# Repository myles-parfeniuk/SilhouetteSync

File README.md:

<ol>
  <li><a href="#about">About</a></li>
  <li><a href="#to-do">To Do</a>
    <ul>
      <li><a href="#hardware">Hardware</a></li>
      <li><a href="#software">Software</a></li>
      <li><a href="#firmware">Firmware</a></li>
    </ul>
  </li>
  <li><a href="#license">License</a></li>
</ol>

## About
Open source motion tracker band intended for athletics analytics.

## To Do

### Hardware
- Decide on full breadth of features ✔️
- Finalize IMU selection ✔️
- Determine user inputs ✔️
- Finalize schematic ✔️
- Finalize layout✔️
- First PCB bring-up
- Test power draw for battery selection
- Design device enclosure

### Software
- Attempt basic plotting ✔️ 
- Decide on choice of language ✔️
- Decide on choice of graphics rendering or plotting library ✔️
- Test animation and basic app layout ✔️
- Write backend for communication with firmware (for prototyping UART/serial can be used)
- Algorithm to derive individual joint angle regardless of absolute body position
- Algorithm to follow through workout and report on effectiveness
- Tracker information screen
 
### Firmware
- Run tests and determine whether WiFi or BLE will be used to communicate with software ✔️
- Write driver for BLE or UDP (maybe TCP?) over WiFi ✔️
- Write driver class for BNO085 SPI IMU ✔️
- Implement addressable LEDs ✔️
- Write battery gauge driver (decided to go with ADC battery measurement)
- Write suit calibration routine 
- Improve wireless stability
- Implement device power up and power sensing algorithm

## License
Distributed under the GNU 3.0 License. See `LICENSE.md` for more information.
<p align="right">(<a href="#readme-top">back to top</a>)</p>

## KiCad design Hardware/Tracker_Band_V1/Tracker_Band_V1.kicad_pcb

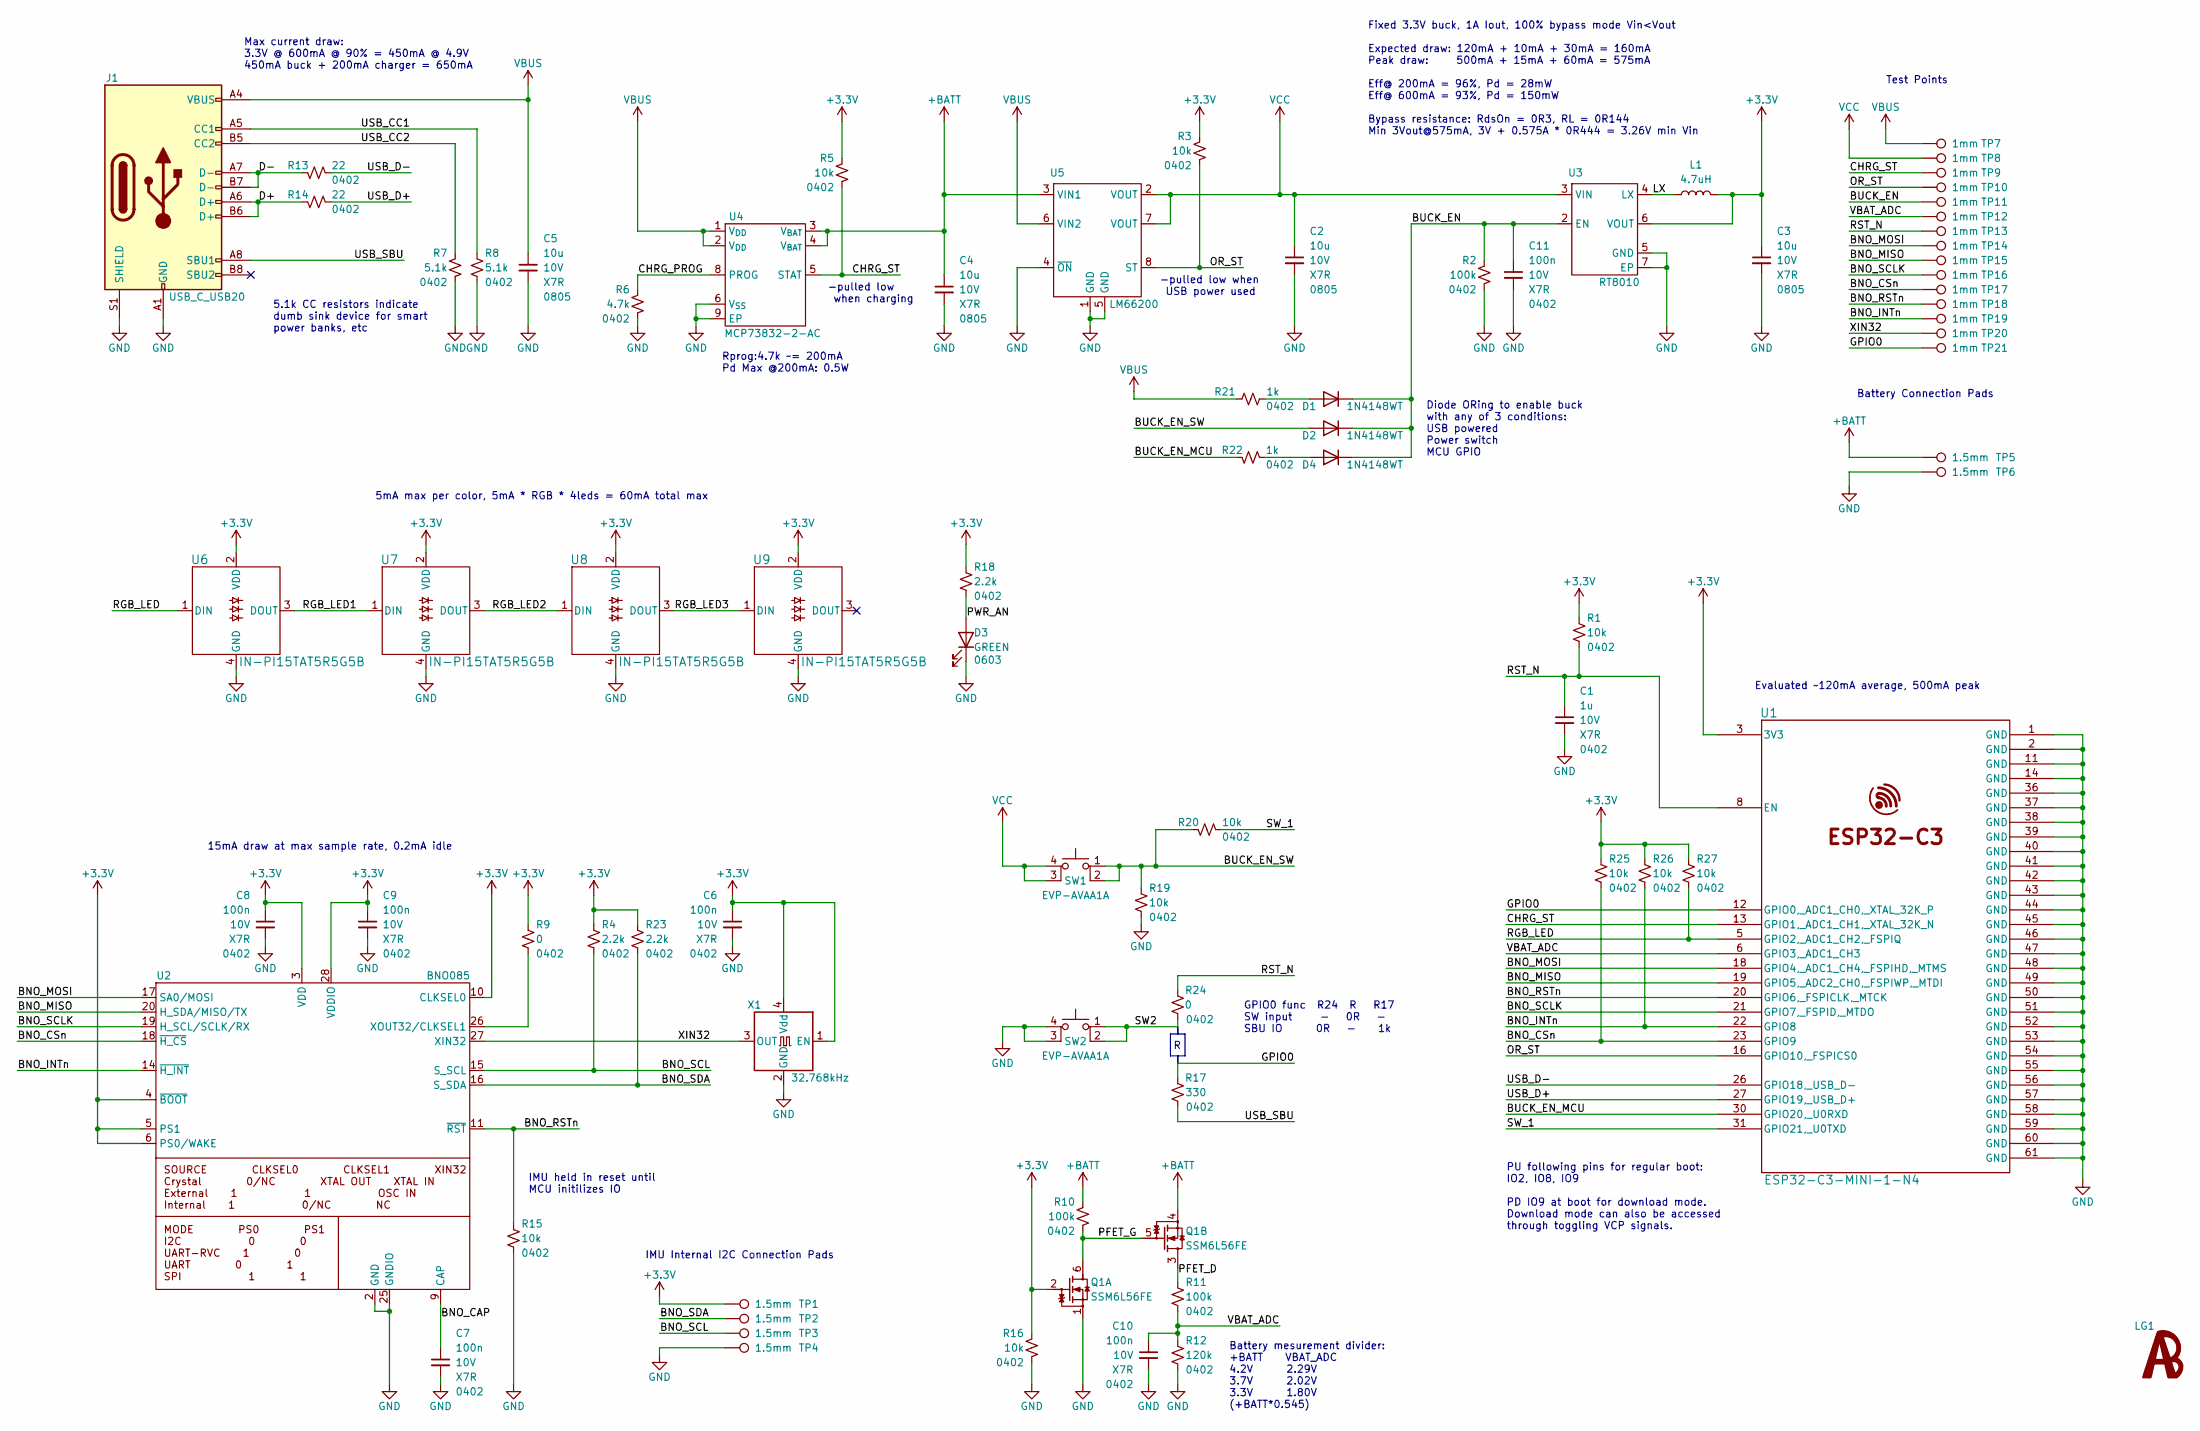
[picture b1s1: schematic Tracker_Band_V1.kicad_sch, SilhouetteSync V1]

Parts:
C1: 1u; C_0402_1005Metric; Voltage 10V
C2, C3, C4, C5: 10u; C_0805_2012Metric; Voltage 10V
C6, C7, C8, C9, C10, C11: 100n; C_0402_1005Metric; Voltage 10V
D1, D2, D4: 1N4148WT; D_SOD-523
D3: GREEN; LED_0603_1608Metric
J1: USB_C_USB20; USB_C_Receptacle_G-Switch_GT-USB-7010ASV_local3d
L1: 4.7uH; L_Taiyo-Yuden_NR-30xx
LG1: AB_logo
Q1: SSM6L56FE; SOT-563
R1, R3, R5, R15, R16, R19, R20, R25, R26, R27: 10k; R_0402_1005Metric
R2, R10, R11: 100k; R_0402_1005Metric
R4, R18, R23: 2.2k; R_0402_1005Metric
R6: 4.7k; R_0402_1005Metric
R7, R8: 5.1k; R_0402_1005Metric
R9, R24: 0; R_0402_1005Metric
R12: 120k; R_0402_1005Metric
R13, R14: 22; R_0402_1005Metric
R17: 330; R_0402_1005Metric
R21, R22: 1k; R_0402_1005Metric
SW1, SW2: EVP-AVAA1A; EVP-AVAA1A_PAN
TP1, TP2, TP3, TP4, TP5, TP6: 1.5mm; TestPoint_Pad_D1.5mm
TP7, TP8, TP9, TP10, TP11, TP12, TP13, TP14, TP15, TP16, TP17, TP18, TP19, TP20, TP21: 1mm; TestPoint_Pad_D1.0mm
U1: ESP32-C3-MINI-1-N4; ESP32-C3-MINI-1_EXP
U2: BNO085; LGA-28_5.2x3.8mm_P0.5mm
U3: RT8010; DFN-6-1EP_2x2mm_P0.65mm_EP1x1.6mm
U4: MCP73832-2-AC; DFN-8-1EP_3x2mm_P0.5mm_EP1.7x1.4mm
U5: LM66200; SOT-5X3_DRL_TEX-L
U6, U7, U8, U9: IN-PI15TAT5R5G5B; IN-PI15_INL
X1: 32.768kHz; OSC_ECS-1618-300-BN-TR

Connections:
+3.3V: C3.1, C6.1, C8.1, C9.1, L1.2, Q1.2 (G), R1.1, R3.1, R4.1, R5.1, R9.1, R16.1, R18.1, R23.1, R25.1, R26.1, R27.1, TP1.1, U1.3 (3V3), U2.3 (VDD), U2.4 (~BOOT), U2.5 (PS1), U2.6 (PS0/WAKE), U2.10 (CLKSEL0), U2.28 (VDDIO), U3.6 (VOUT), U6.2 (VDD), U7.2 (VDD), U8.2 (VDD), U9.2 (VDD), X1.1 (EN), X1.4 (Vdd)
+BATT: C4.1, Q1.4 (1), R10.1, TP5.1, U4.3 (V_{BAT}), U4.4 (V_{BAT}), U5.3 (VIN1)
/BNO_CAP: C7.1, U2.9 (CAP)
/BNO_CSn: R25.2, TP17.1, U1.23 (GPIO9), U2.18 (~H_CS)
/BNO_INTn: R26.2, TP19.1, U1.22 (GPIO8), U2.14 (~H_INT)
/BNO_MISO: TP15.1, U1.19 (GPIO5,_ADC2_CH0,_FSPIWP,_MTDI), U2.20 (H_SDA/MISO/TX)
/BNO_MOSI: TP14.1, U1.18 (GPIO4,_ADC1_CH4,_FSPIHD,_MTMS), U2.17 (SA0/MOSI)
/BNO_RSTn: R15.1, TP18.1, U1.20 (GPIO6,_FSPICLK,_MTCK), U2.11 (~RST)
/BNO_SCL: R4.2, TP3.1, U2.15 (S_SCL)
/BNO_SCLK: TP16.1, U1.21 (GPIO7,_FSPID,_MTDO), U2.19 (H_SCL/SCLK/RX)
/BNO_SDA: R23.2, TP2.1, U2.16 (S_SDA)
/BUCK_EN: C11.1, D1.1 (K), D2.1 (K), D4.1 (K), R2.1, TP11.1, U3.2 (EN)
/BUCK_EN_MCU: R22.1, U1.30 (GPIO20,_U0RXD)
/BUCK_EN_SW: D2.2 (A), R19.1, R20.1, SW1.1, SW1.2
/CHRG_PROG: R6.1, U4.8 (PROG)
/CHRG_ST: R5.2, TP9.1, U1.13 (GPIO1,_ADC1_CH1,_XTAL_32K_N), U4.5 (STAT)
/D+: J1.A6 (D+), J1.B6 (D+), R14.1
/D-: J1.A7 (D-), J1.B7 (D-), R13.1
/GPIO0: R17.2, TP21.1, U1.12 (GPIO0,_ADC1_CH0,_XTAL_32K_P)
/LX: L1.1, U3.4 (LX)
/OR_ST: R3.2, TP10.1, U1.16 (GPIO10,_FSPICS0), U5.8 (ST)
/PFET_D: Q1.3 (D), R11.1
/PFET_G: Q1.5 (G), Q1.6 (D), R10.2
/PWR_AN: D3.2 (A), R18.2
/RGB_LED: R27.2, U1.5 (GPIO2,_ADC1_CH2,_FSPIQ), U6.1 (DIN)
/RGB_LED1: U6.3 (DOUT), U7.1 (DIN)
/RGB_LED2: U7.3 (DOUT), U8.1 (DIN)
/RGB_LED3: U8.3 (DOUT), U9.1 (DIN)
/RST_N: C1.1, R1.2, R24.2, TP13.1, U1.8 (EN)
/SW2: R24.1, SW2.1, SW2.2
/SW_1: R20.2, U1.31 (GPIO21,_U0TXD)
/USB_CC1: J1.A5 (CC1), R8.1
/USB_CC2: J1.B5 (CC2), R7.1
/USB_D+: R14.2, U1.27 (GPIO19,_USB_D+)
/USB_D-: R13.2, U1.26 (GPIO18,_USB_D-)
/USB_SBU: J1.A8 (SBU1), R17.1
/VBAT_ADC: C10.1, R11.2, R12.1, TP12.1, U1.6 (GPIO3,_ADC1_CH3)
/XIN32: TP20.1, U2.27 (XIN32), X1.3 (OUT)
GND: C1.2, C2.2, C3.2, C4.2, C5.2, C6.2, C7.2, C8.2, C9.2, C10.2, C11.2, D3.1 (K), J1.A1 (GND), J1.A12 (GND), J1.B1 (GND), J1.B12 (GND), J1.S1 (SHIELD), Q1.1 (S), R2.2, R6.2, R7.2, R8.2, R12.2, R15.2, R16.2, R19.2, SW2.3 (K), SW2.4 (A), TP4.1, TP6.1, U1.1 (GND), U1.2 (GND), U1.11 (GND), U1.14 (GND), U1.36 (GND), U1.37 (GND), U1.38 (GND), U1.39 (GND), U1.40 (GND), U1.41 (GND), U1.42 (GND), U1.43 (GND), U1.44 (GND), U1.45 (GND), U1.46 (GND), U1.47 (GND), U1.48 (GND), U1.49 (GND), U1.50 (GND), U1.51 (GND), U1.52 (GND), U1.53 (GND), U1.54 (GND), U1.55 (GND), U1.56 (GND), U1.57 (GND), U1.58 (GND), U1.59 (GND), U1.60 (GND), U1.61 (GND), U2.2 (GND), U2.25 (GNDIO), U3.5 (GND), U3.7 (EP), U4.6 (V_{SS}), U4.9 (EP), U5.1 (GND), U5.4 (~ON), U5.5 (GND), U6.4 (GND), U7.4 (GND), U8.4 (GND), U9.4 (GND), X1.2 (GND)
unnamed: D1.2 (A), R21.2
unnamed: D4.2 (A), R22.2
unnamed: R9.2, U2.26 (XOUT32/CLKSEL1)
VBUS: C5.1, J1.A4 (VBUS), J1.A9 (VBUS), J1.B4 (VBUS), J1.B9 (VBUS), R21.1, TP7.1, U4.1 (V_{DD}), U4.2 (V_{DD}), U5.6 (VIN2)
VCC: C2.1, SW1.3 (K), SW1.4 (A), TP8.1, U3.3 (VIN), U5.2 (VOUT), U5.7 (VOUT)

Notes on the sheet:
PU following pins for regular boot: IO2, IO8, IO9 PD IO9 at boot for download mode. Download mode can also be accessed through toggling VCP signals.
Evaluated ~120mA average, 500mA peak
Diode ORing to enable buck with any of 3 conditions: USB powered Power switch MCU GPIO
Battery mesurement divider: +BATT VBAT_ADC 4.2V 2.29V 3.7V 2.02V 3.3V 1.80V (+BATT*0.545)
IMU Internal I2C Connection Pads
-pulled low when charging
Fixed 3.3V buck, 1A Iout, 100% bypass mode Vin<Vout Expected draw: 120mA + 10mA + 30mA = 160mA Peak draw: 500mA + 15mA + 60mA = 575mA Eff@ 200mA = 96%, Pd = 28mW Eff@ 600mA = 93%, Pd = 150mW Bypass resistance: RdsOn = 0R3, RL = 0R144 Min 3Vout@575mA, 3V + 0.575A * 0R444 = 3.26V min Vin
Max current draw: 3.3V @ 600mA @ 90% = 450mA @ 4.9V 450mA buck + 200mA charger = 650mA
-pulled low when USB power used
5.1k CC resistors indicate dumb sink device for smart power banks, etc
Test Points
IMU held in reset until MCU initilizes IO
GPIO0 func R24 R R17 SW input - 0R - SBU IO 0R - 1k
Battery Connection Pads
15mA draw at max sample rate, 0.2mA idle
5mA max per color, 5mA * RGB * 4leds = 60mA total max
Rprog:4.7k ~= 200mA Pd Max @200mA: 0.5W

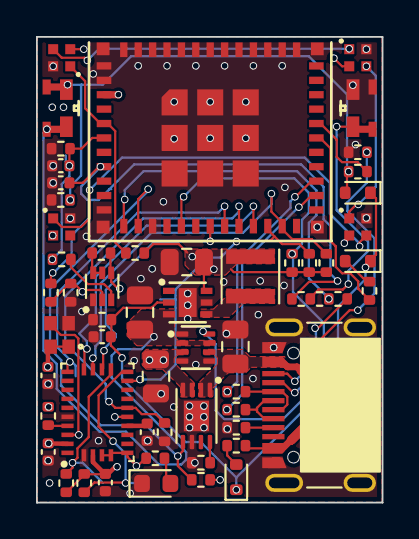
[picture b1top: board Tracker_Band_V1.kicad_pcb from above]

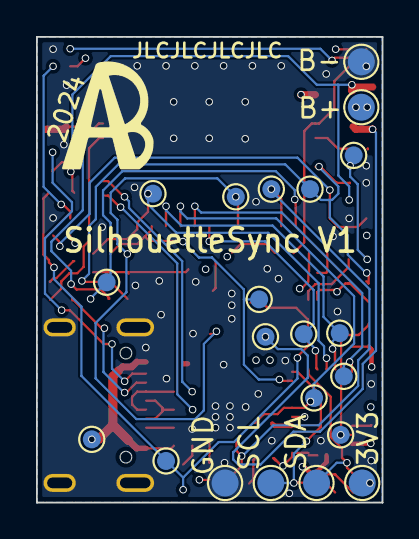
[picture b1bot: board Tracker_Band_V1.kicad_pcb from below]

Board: 4 copper layers, 19.2 x 25.9 mm, 79 parts (22 on the bottom side), 44 nets.

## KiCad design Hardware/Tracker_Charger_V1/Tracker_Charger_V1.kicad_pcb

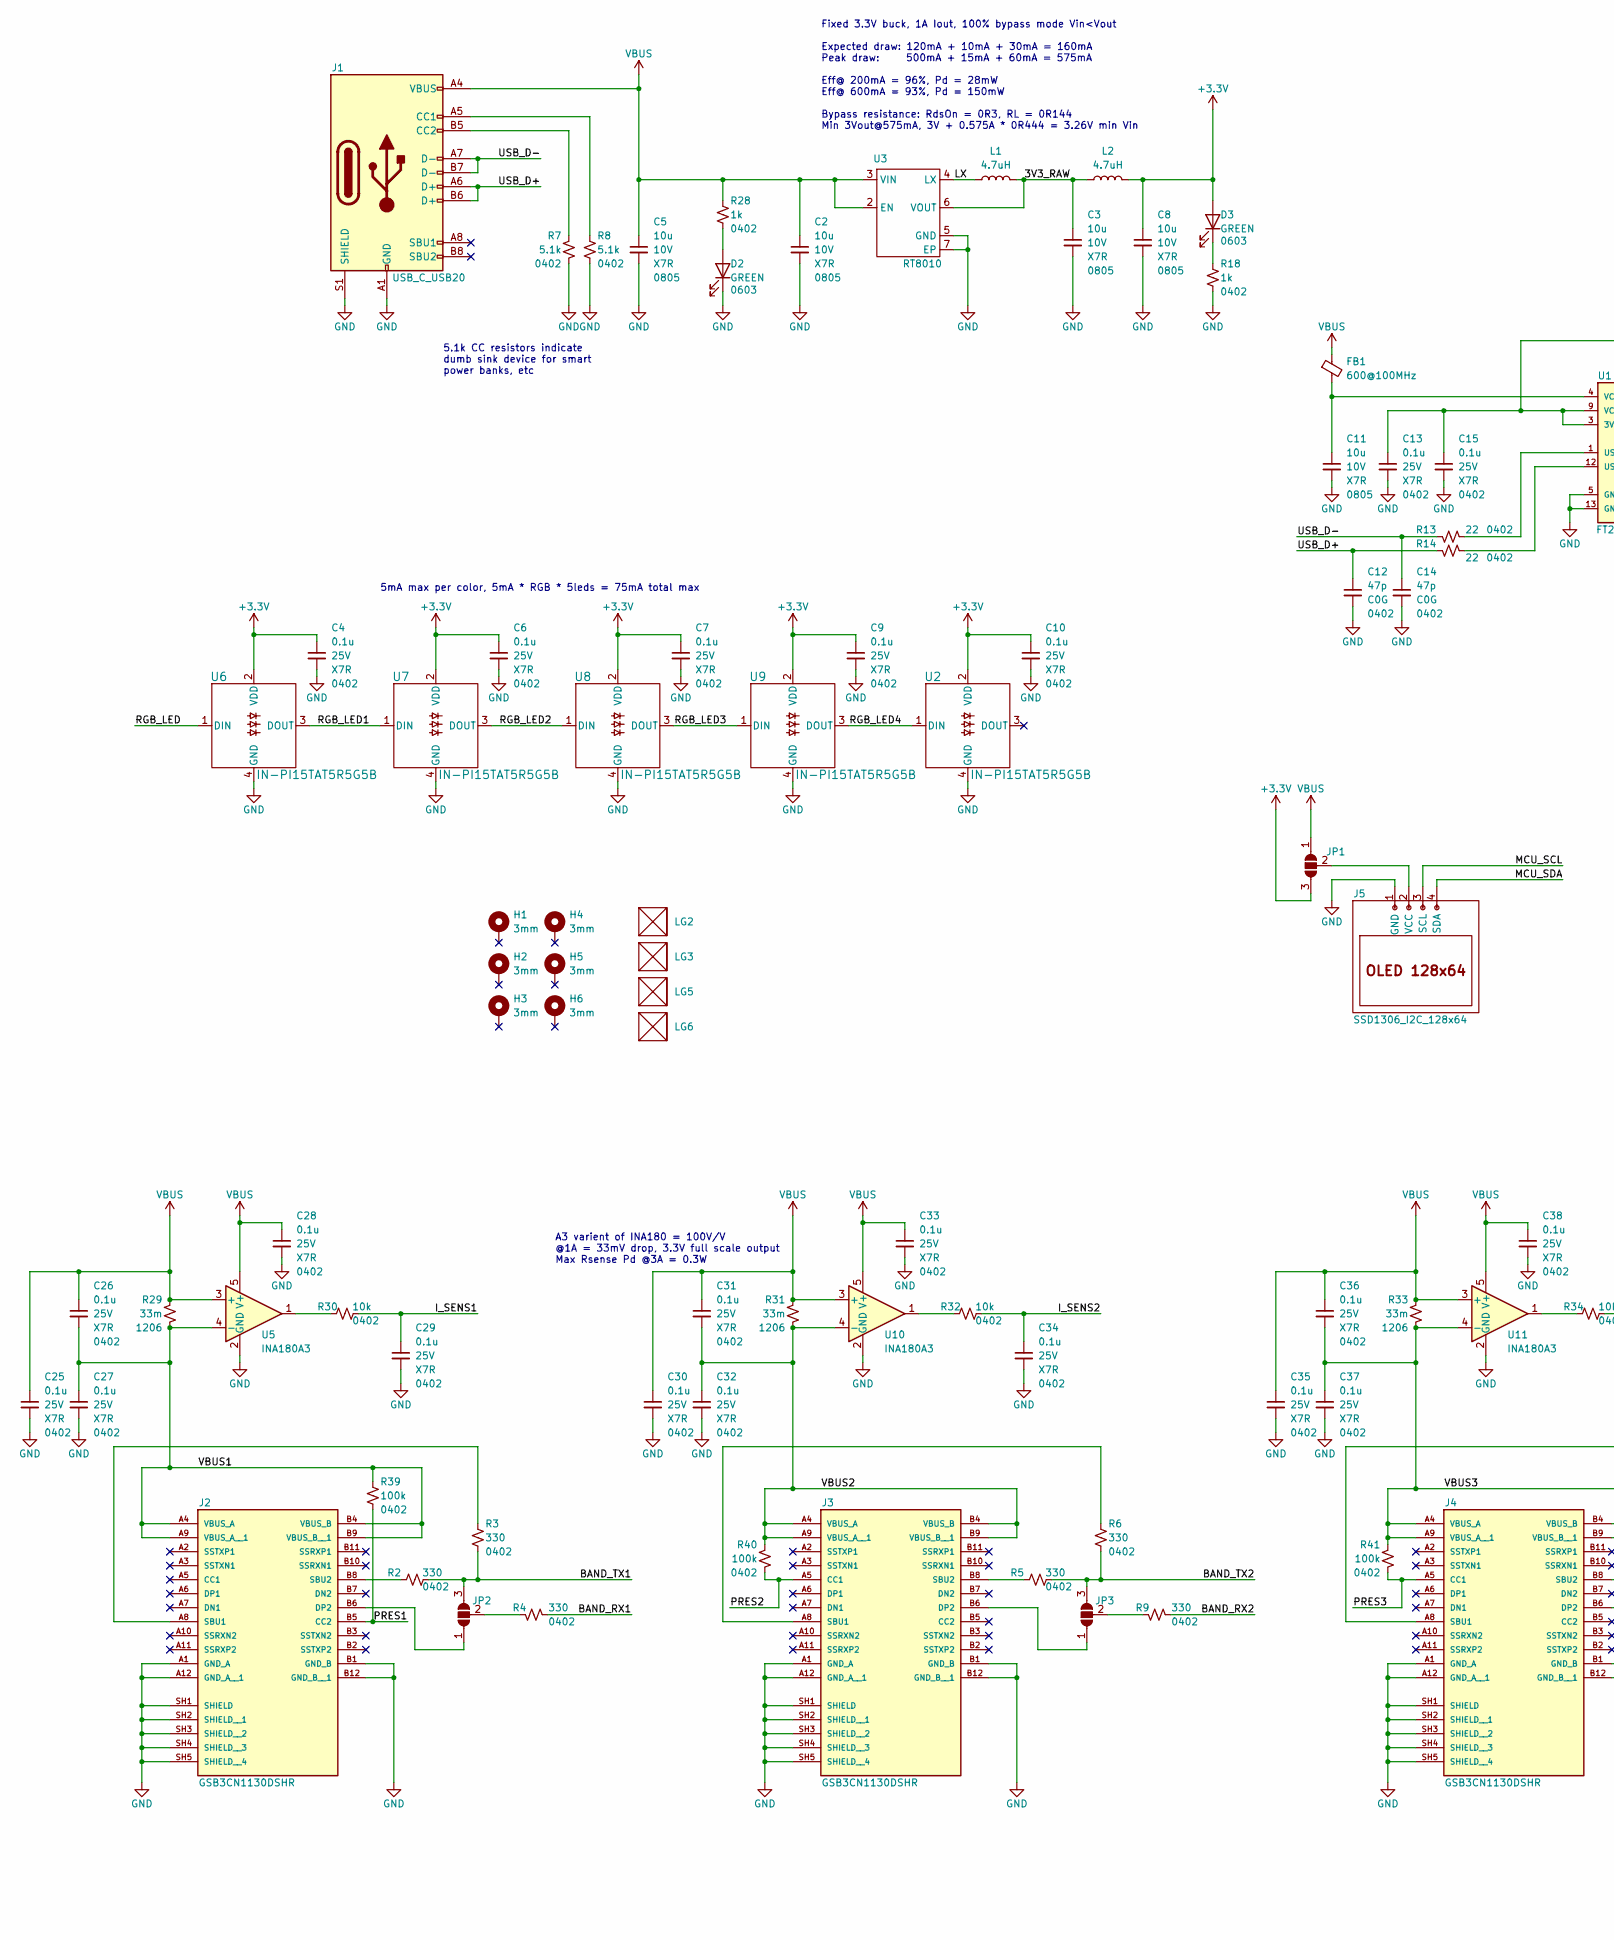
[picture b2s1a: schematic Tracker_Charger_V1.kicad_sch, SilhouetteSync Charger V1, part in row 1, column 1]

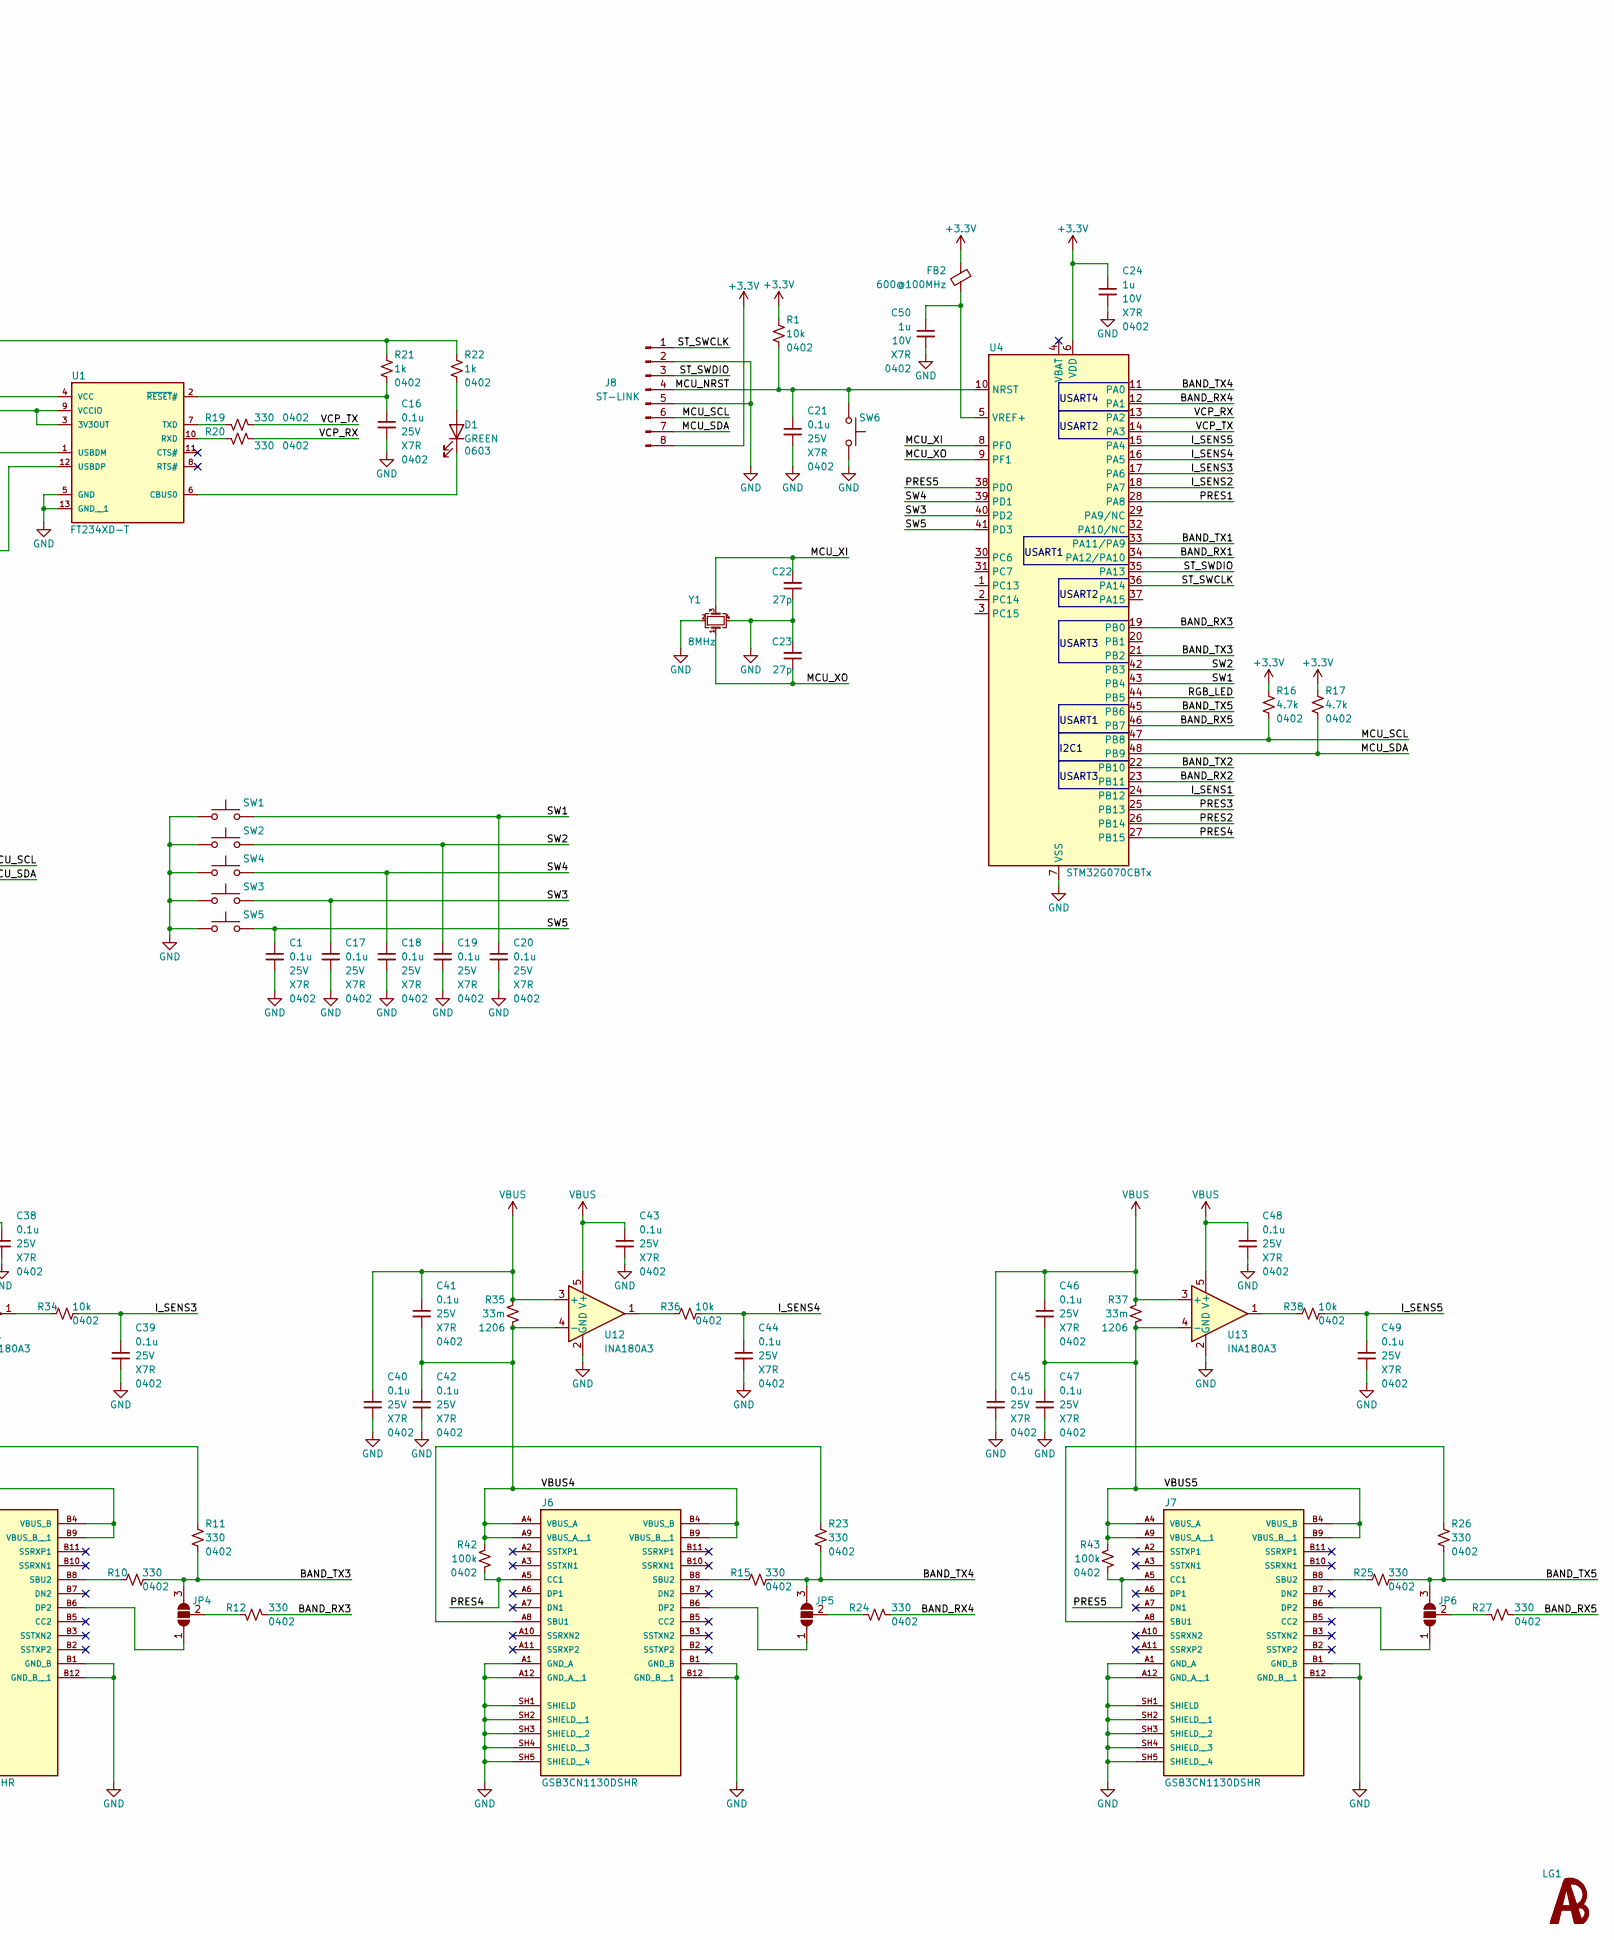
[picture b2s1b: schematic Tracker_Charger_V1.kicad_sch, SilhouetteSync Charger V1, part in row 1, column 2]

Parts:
C1, C4, C6, C7, C9, C10, C13, C15, C16, C17, C18, C19, C20, C21, C25, C26, C27, C28, C29, C30, C31, C32, C33, C34, C35, C36, C37, C38, C39, C40, C41, C42, C43, C44, C45, C46, C47, C48, C49: 0.1u; C_0402_1005Metric; Voltage 25V
C2, C3, C5, C8, C11: 10u; C_0805_2012Metric; Voltage 10V
C12, C14: 47p; C_0402_1005Metric; Voltage 25V
C22, C23: 27p; C_0402_1005Metric
C24, C50: 1u; C_0402_1005Metric; Voltage 10V
D1, D2, D3: GREEN; LED_0603_1608Metric
FB1, FB2: 600@100MHz; R_0402_1005Metric
H1, H2, H3, H4, H5, H6: 3mm; MountingHole_3mm_Pad_Via
J1: USB_C_USB20; USB_C_Receptacle_G-Switch_GT-USB-7010ASV_local3d
J2, J3, J4, J6, J7: GSB3CN1130DSHR; AMPHENOL_GSB3CN1130DSHR_NEW1; PARTREV AX1
J5: SSD1306_I2C_128x64; SSD1306_12864_I2C_13in
J8: ST-LINK; PinHeader_1x08_P2.54mm_Horizontal
JP1, JP2, JP3, JP4, JP5, JP6: SolderJumper_3_Open; SolderJumper-3_P1.3mm_Open_RoundedPad1.0x1.5mm_NumberLabels
L1, L2: 4.7uH; L_Taiyo-Yuden_NR-30xx
LG1: AB_logo
LG2: run_silk_14mm
LG3: bench_silk_14mm
LG5: hike_silk_14mm
LG6: squat_silk_14mm
R1, R30, R32, R34, R36, R38: 10k; R_0402_1005Metric
R2, R3, R4, R5, R6, R9, R10, R11, R12, R15, R19, R20, R23, R24, R25, R26, R27: 330; R_0402_1005Metric
R7, R8: 5.1k; R_0402_1005Metric
R13, R14: 22; R_0402_1005Metric
R16, R17: 4.7k; R_0402_1005Metric
R18, R21, R22, R28: 1k; R_0402_1005Metric
R29, R31, R33, R35, R37: 33m; R_1206_3216Metric
R39, R40, R41, R42, R43: 100k; R_0402_1005Metric
SW1, SW2, SW3, SW4, SW5, SW6: SW_Push; SW_SPST_CK_RS282G05A3
U1: FT234XD-T; DFN-12-1EP_3x3mm_P0.45mm_EP1.66x2.38mm
U2, U6, U7, U8, U9: IN-PI15TAT5R5G5B; IN-PI15_INL
U3: RT8010; DFN-6-1EP_2x2mm_P0.65mm_EP1x1.6mm
U4: STM32G070CBTx; LQFP-48_7x7mm_P0.5mm
U5, U10, U11, U12, U13: INA180A3; SOT-23-5
Y1: 8MHz; Crystal_SMD_Abracon_ABM8G-4Pin_3.2x2.5mm

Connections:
+3.3V: C4.1, C6.1, C7.1, C8.1, C9.1, C10.1, C24.1, D3.2 (A), FB2.1, J8.8, JP1.3 (B), L2.2, R1.1, R16.1, R17.1, U2.2 (VDD), U4.6 (VDD), U6.2 (VDD), U7.2 (VDD), U8.2 (VDD), U9.2 (VDD)
/3V3_RAW: C3.1, L1.2, L2.1, U3.6 (VOUT)
/BAND_RX1: R4.2, U4.34 (PA12/PA10)
/BAND_RX2: R9.2, U4.23 (PB11)
/BAND_RX3: R12.2, U4.19 (PB0)
/BAND_RX4: R24.2, U4.12 (PA1)
/BAND_RX5: R27.2, U4.46 (PB7)
/BAND_TX1: JP2.3 (B), R2.1, R3.2, U4.33 (PA11/PA9)
/BAND_TX2: JP3.3 (B), R5.1, R6.2, U4.22 (PB10)
/BAND_TX3: JP4.3 (B), R10.1, R11.2, U4.21 (PB2)
/BAND_TX4: JP5.3 (B), R15.1, R23.2, U4.11 (PA0)
/BAND_TX5: JP6.3 (B), R25.1, R26.2, U4.45 (PB6)
/I_SENS1: C29.1, R30.1, U4.24 (PB12)
/I_SENS2: C34.1, R32.1, U4.18 (PA7)
/I_SENS3: C39.1, R34.1, U4.17 (PA6)
/I_SENS4: C44.1, R36.1, U4.16 (PA5)
/I_SENS5: C49.1, R38.1, U4.15 (PA4)
/LX: L1.1, U3.4 (LX)
/MCU_NRST: C21.1, J8.4, R1.2, SW6.1, U4.10 (NRST)
/MCU_SCL: J5.3 (SCL), J8.6, R16.2, U4.47 (PB8)
/MCU_SDA: J5.4 (SDA), J8.7, R17.2, U4.48 (PB9)
/MCU_XI: C22.2, U4.8 (PF0), Y1.3
/MCU_XO: C23.1, U4.9 (PF1), Y1.1
/PRES1: J2.B5 (CC2), R39.2, U4.28 (PA8)
/PRES2: J3.A5 (CC1), R40.2, U4.26 (PB14)
/PRES3: J4.A5 (CC1), R41.2, U4.25 (PB13)
/PRES4: J6.A5 (CC1), R42.2, U4.27 (PB15)
/PRES5: J7.A5 (CC1), R43.2, U4.38 (PD0)
/RGB_LED: U4.44 (PB5), U6.1 (DIN)
/RGB_LED1: U6.3 (DOUT), U7.1 (DIN)
/RGB_LED2: U7.3 (DOUT), U8.1 (DIN)
/RGB_LED3: U8.3 (DOUT), U9.1 (DIN)
/RGB_LED4: U2.1 (DIN), U9.3 (DOUT)
/ST_SWCLK: J8.1, U4.36 (PA14)
/ST_SWDIO: J8.3, U4.35 (PA13)
/SW1: C20.1, SW1.2, U4.43 (PB4)
/SW2: C19.1, SW2.2, U4.42 (PB3)
/SW3: C17.1, SW3.2, U4.40 (PD2)
/SW4: C18.1, SW4.2, U4.39 (PD1)
/SW5: C1.1, SW5.2, U4.41 (PD3)
/USB_D+: C12.1, J1.A6 (D+), J1.B6 (D+), R14.1
/USB_D-: C14.1, J1.A7 (D-), J1.B7 (D-), R13.1
/VBUS1: C26.2, C27.1, J2.A4 (VBUS_A), J2.A9 (VBUS_A__1), J2.B4 (VBUS_B), J2.B9 (VBUS_B__1), R29.2, R39.1, U5.4 (-)
/VBUS2: C31.2, C32.1, J3.A4 (VBUS_A), J3.A9 (VBUS_A__1), J3.B4 (VBUS_B), J3.B9 (VBUS_B__1), R31.2, R40.1, U10.4 (-)
/VBUS3: C36.2, C37.1, J4.A4 (VBUS_A), J4.A9 (VBUS_A__1), J4.B4 (VBUS_B), J4.B9 (VBUS_B__1), R33.2, R41.1, U11.4 (-)
/VBUS4: C41.2, C42.1, J6.A4 (VBUS_A), J6.A9 (VBUS_A__1), J6.B4 (VBUS_B), J6.B9 (VBUS_B__1), R35.2, R42.1, U12.4 (-)
/VBUS5: C46.2, C47.1, J7.A4 (VBUS_A), J7.A9 (VBUS_A__1), J7.B4 (VBUS_B), J7.B9 (VBUS_B__1), R37.2, R43.1, U13.4 (-)
/VCP_RX: R20.2, U4.13 (PA2)
/VCP_TX: R19.2, U4.14 (PA3)
GND: C1.2, C2.2, C3.2, C4.2, C5.2, C6.2, C7.2, C8.2, C9.2, C10.2, C11.2, C12.2, C13.2, C14.2, C15.2, C16.2, C17.2, C18.2, C19.2, C20.2, C21.2, C22.1, C23.2, C24.2, C25.2, C27.2, C28.2, C29.2, C30.2, C32.2, C33.2, C34.2, C35.2, C37.2, C38.2, C39.2, C40.2, C42.2, C43.2, C44.2, C45.2, C47.2, C48.2, C49.2, C50.2, D2.1 (K), J1.A1 (GND), J1.A12 (GND), J1.B1 (GND), J1.B12 (GND), J1.S1 (SHIELD), J2.A1 (GND_A), J2.A12 (GND_A__1), J2.B1 (GND_B), J2.B12 (GND_B__1), J2.SH1 (SHIELD), J2.SH2 (SHIELD__1), J2.SH3 (SHIELD__2), J2.SH4 (SHIELD__3), J2.SH5 (SHIELD__4), J3.A1 (GND_A), J3.A12 (GND_A__1), J3.B1 (GND_B), J3.B12 (GND_B__1), J3.SH1 (SHIELD), J3.SH2 (SHIELD__1), J3.SH3 (SHIELD__2), J3.SH4 (SHIELD__3), J3.SH5 (SHIELD__4), J4.A1 (GND_A), J4.A12 (GND_A__1), J4.B1 (GND_B), J4.B12 (GND_B__1), J4.SH1 (SHIELD), J4.SH2 (SHIELD__1), J4.SH3 (SHIELD__2), J4.SH4 (SHIELD__3), J4.SH5 (SHIELD__4), J5.1 (GND), J6.A1 (GND_A), J6.A12 (GND_A__1), J6.B1 (GND_B), J6.B12 (GND_B__1), J6.SH1 (SHIELD), J6.SH2 (SHIELD__1), J6.SH3 (SHIELD__2), J6.SH4 (SHIELD__3), J6.SH5 (SHIELD__4), J7.A1 (GND_A), J7.A12 (GND_A__1), J7.B1 (GND_B), J7.B12 (GND_B__1), J7.SH1 (SHIELD), J7.SH2 (SHIELD__1), J7.SH3 (SHIELD__2), J7.SH4 (SHIELD__3), J7.SH5 (SHIELD__4), J8.2, J8.5, R7.2, R8.2, R18.2, SW1.1, SW2.1, SW3.1, SW4.1, SW5.1, SW6.2, U1.5 (GND), U1.13 (GND__1), U2.4 (GND), U3.5 (GND), U3.7 (EP), U4.7 (VSS), U5.2 (GND), U6.4 (GND), U7.4 (GND), U8.4 (GND), U9.4 (GND), U10.2 (GND), U11.2 (GND), U12.2 (GND), U13.2 (GND), Y1.2, Y1.4
unnamed: D1.2 (A), R22.2
unnamed: D1.1 (K), U1.6 (CBUS0)
unnamed: D2.2 (A), R28.2
unnamed: D3.1 (K), R18.1
unnamed: J1.A5 (CC1), R8.1
unnamed: J1.B5 (CC2), R7.1
unnamed: J2.B6 (DP2), JP2.1 (A)
unnamed: J2.A8 (SBU1), R3.1
unnamed: J2.B8 (SBU2), R2.2
unnamed: J3.B6 (DP2), JP3.1 (A)
unnamed: J3.A8 (SBU1), R6.1
unnamed: J3.B8 (SBU2), R5.2
unnamed: J4.B6 (DP2), JP4.1 (A)
unnamed: J4.A8 (SBU1), R11.1
unnamed: J4.B8 (SBU2), R10.2
unnamed: J5.2 (VCC), JP1.2 (C)
unnamed: J6.B6 (DP2), JP5.1 (A)
unnamed: J6.A8 (SBU1), R23.1
unnamed: J6.B8 (SBU2), R15.2
unnamed: J7.B6 (DP2), JP6.1 (A)
unnamed: J7.A8 (SBU1), R26.1
unnamed: J7.B8 (SBU2), R25.2
unnamed: JP2.2 (C), R4.1
unnamed: JP3.2 (C), R9.1
unnamed: JP4.2 (C), R12.1
unnamed: JP5.2 (C), R24.1
unnamed: JP6.2 (C), R27.1
unnamed: R30.2, U5.1
unnamed: R32.2, U10.1
unnamed: R34.2, U11.1
unnamed: R36.2, U12.1
unnamed: R38.2, U13.1
unnamed: C13.1, C15.1, R21.1, R22.1, U1.3 (3V3OUT), U1.9 (VCCIO)
unnamed: R20.1, U1.10 (RXD)
unnamed: R19.1, U1.7 (TXD)
unnamed: R13.2, U1.1 (USBDM)
unnamed: R14.2, U1.12 (USBDP)
unnamed: C11.1, FB1.2, U1.4 (VCC)
unnamed: C16.1, R21.2, U1.2 (~RESET#)
unnamed: C50.1, FB2.2, U4.5 (VREF+)
VBUS: C2.1, C5.1, C25.1, C26.1, C28.1, C30.1, C31.1, C33.1, C35.1, C36.1, C38.1, C40.1, C41.1, C43.1, C45.1, C46.1, C48.1, FB1.1, J1.A4 (VBUS), J1.A9 (VBUS), J1.B4 (VBUS), J1.B9 (VBUS), JP1.1 (A), R28.1, R29.1, R31.1, R33.1, R35.1, R37.1, U3.2 (EN), U3.3 (VIN), U5.3 (+), U5.5 (V+), U10.3 (+), U10.5 (V+), U11.3 (+), U11.5 (V+), U12.3 (+), U12.5 (V+), U13.3 (+), U13.5 (V+)

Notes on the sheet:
USART1
USART4
USART2
Fixed 3.3V buck, 1A Iout, 100% bypass mode Vin<Vout Expected draw: 120mA + 10mA + 30mA = 160mA Peak draw: 500mA + 15mA + 60mA = 575mA Eff@ 200mA = 96%, Pd = 28mW Eff@ 600mA = 93%, Pd = 150mW Bypass resistance: RdsOn = 0R3, RL = 0R144 Min 3Vout@575mA, 3V + 0.575A * 0R444 = 3.26V min Vin
USART3
5.1k CC resistors indicate dumb sink device for smart power banks, etc
I2C1
A3 varient of INA180 = 100V/V @1A = 33mV drop, 3.3V full scale output Max Rsense Pd @3A = 0.3W
5mA max per color, 5mA * RGB * 5leds = 75mA total max

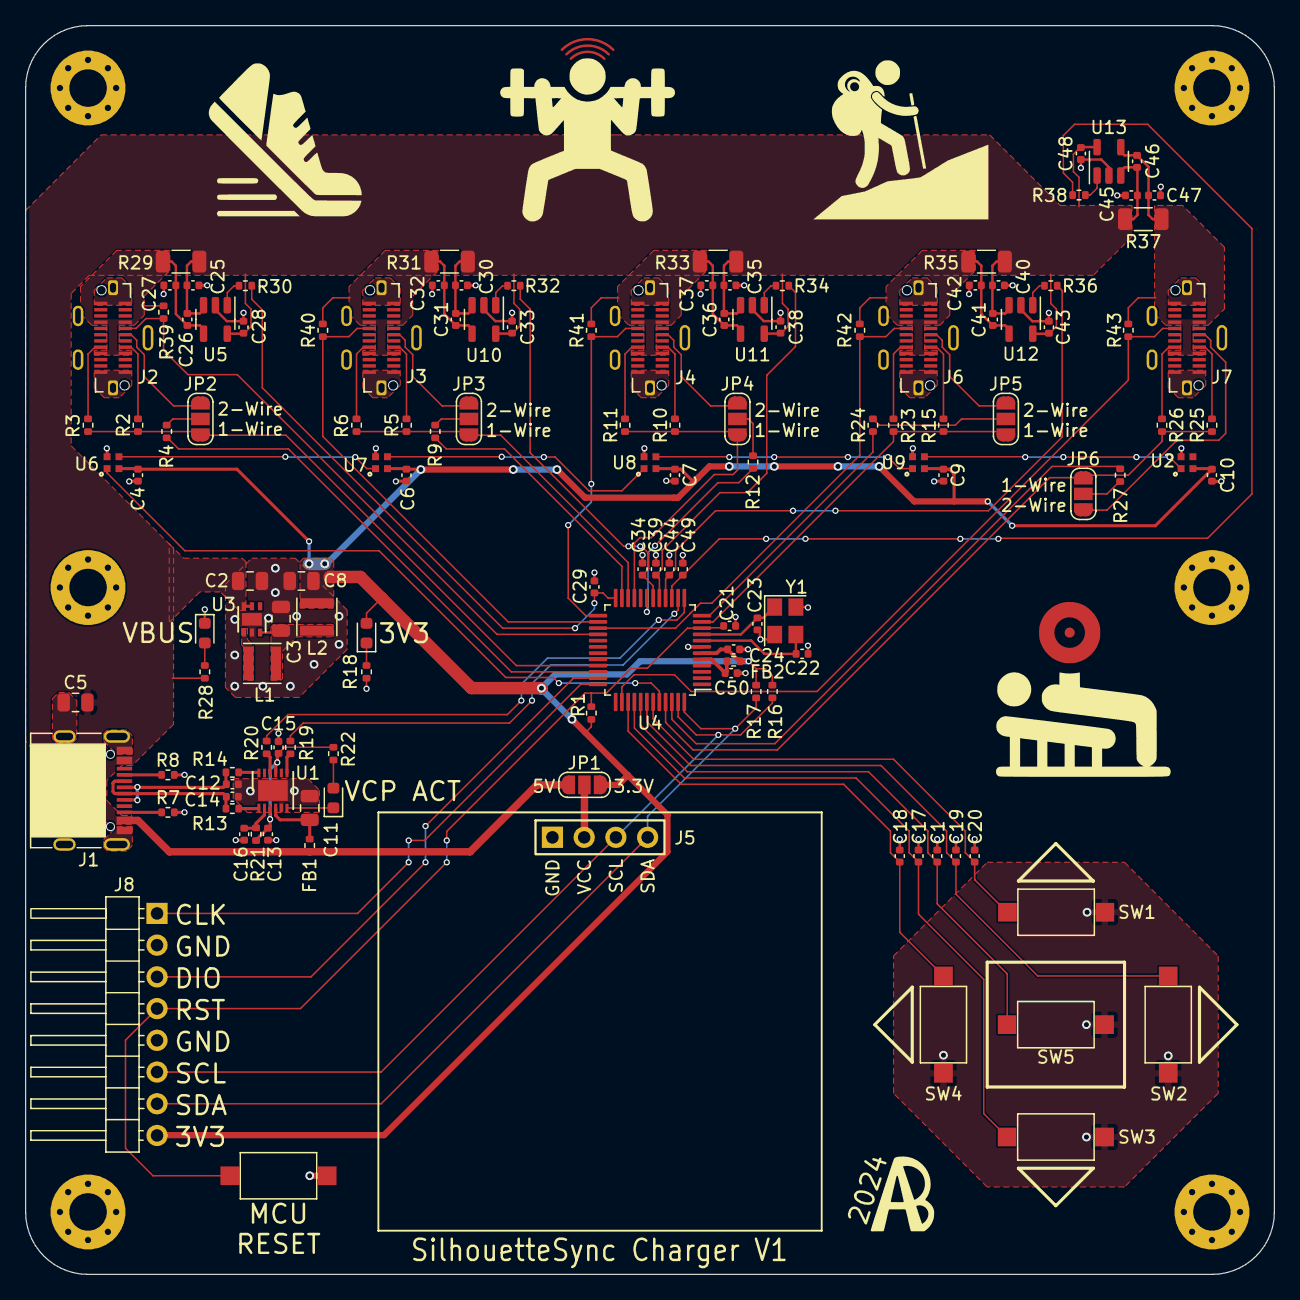
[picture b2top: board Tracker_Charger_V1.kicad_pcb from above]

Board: 2 copper layers, 100.0 x 100.0 mm, 145 parts (0 on the bottom side), 91 nets.

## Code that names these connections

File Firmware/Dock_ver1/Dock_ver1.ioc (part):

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Mcu.Name=STM32G070CBTx
Mcu.Package=LQFP48
Mcu.UserName=STM32G070CBTx
PA13.Mode=Serial_Wire
PA13.Signal=SYS_SWDIO
PA14-BOOT0.Mode=Serial_Wire
PA14-BOOT0.Signal=SYS_SWCLK
PA2.Mode=Asynchronous
PA2.Signal=USART2_TX
PA3.Mode=Asynchronous
PA3.Signal=USART2_RX
PA4.Mode=IN4
PA4.Signal=ADC1_IN4
PA5.Mode=IN5
PA5.Signal=ADC1_IN5
PA6.Mode=IN6
PA6.Signal=ADC1_IN6
PA7.Mode=IN7
PA7.Signal=ADC1_IN7
PA8.Signal=GPIO_Input
PB12.Mode=IN16
PB12.Signal=ADC1_IN16
PB13.Signal=GPIO_Input
PB14.Signal=GPIO_Input
PB15.Signal=GPIO_Input
PB3.GPIOParameters=GPIO_PuPd
PB3.GPIO_PuPd=GPIO_PULLUP
PB3.Signal=GPIO_Input
PB4.GPIOParameters=GPIO_PuPd
PB4.GPIO_PuPd=GPIO_PULLUP
PB4.Signal=GPIO_Input
PB5.Signal=GPIO_Output
PB8.Mode=I2C
PB8.Signal=I2C1_SCL
PB9.Mode=I2C
PB9.Signal=I2C1_SDA
PD0.Signal=GPIO_Input
PD1.GPIOParameters=GPIO_PuPd
PD1.GPIO_PuPd=GPIO_PULLUP
PD1.Signal=GPIO_Input
PD2.GPIOParameters=GPIO_PuPd
PD2.GPIO_PuPd=GPIO_PULLUP
PD2.Signal=GPIO_Input
PD3.GPIOParameters=GPIO_PuPd
PD3.GPIO_PuPd=GPIO_PULLUP
PD3.Signal=GPIO_Input
PF0-OSC_IN\ (PF0).Mode=HSE-External-Oscillator
PF0-OSC_IN\ (PF0).Signal=RCC_OSC_IN
PF1-OSC_OUT\ (PF1).Mode=HSE-External-Oscillator
PF1-OSC_OUT\ (PF1).Signal=RCC_OSC_OUT
RCC.HSE_VALUE=8000000
RCC.SYSCLKFreq_VALUE=64000000
RCC.SYSCLKSource=RCC_SYSCLKSOURCE_PLLCLK
board=custom

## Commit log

2023-09-28 updated: README.md, project directory structure
2023-09-28 Fixed banner image
2023-09-28 test
2023-09-29 Firmware framework
2023-10-04 implemented nav switch driver
2023-10-04 added git ignore
2023-10-04 removed all submodules
2023-10-04 fixed submodules
2023-10-04 Fixed submodules (this time for real)
2023-10-04 Implement cpp fork of u8g2 HAL compatability component
2023-10-04 Fixed NavSwitchDriver issue
2023-10-04 integrated display into device model
2023-10-04 implemented gui_core menu drawing task
2023-10-04 Fixed submodules (again)
2023-10-04 Changed debug serial rate to 921600baud
2023-10-05 Implemented menu engine
2023-10-05 Updated data control submodule
2023-10-05 Updated menu engine documentation
2023-10-06 Implemented IMU driver
2023-10-09 my first commit
2023-10-09 My second test commit
2023-11-13 Implemented BNO085 sensor
2023-11-13 Updated nav switch driver
2023-11-14 Implemented new nav switch driver
2023-11-14 Added python cube visualizer for testing IMU.
2023-11-14 Updated submodules
2024-01-10 added TCP server
2024-01-10 Added PC TCP client testing script
2024-01-10 updated pyTestingClient comments
2024-01-10 Unity Wireless Cube Visualization
2024-01-17 Added schematic
2024-01-17 added buck calcs
2024-01-18 ADC data logging script and firmware
2024-01-18 Modified README.md, removed redundant file extension
2024-01-19 added custom power sym/fp
2024-01-21 Added Test results, removed sample cap
2024-01-21 added 1500mAh battery test
2024-02-01 Eliminated NavSwitch & OLED Support, upated BNO08x submodule
2024-02-01 esp32C3 port
2024-02-05 Updated schematic wiring
2024-02-05 Added LED indicator driver
2024-02-05 UnityAppV1.0
2024-02-07 Updated TCPServer
2024-02-07 fixed LED connection indicator
2024-02-07 UnityApp1.02
2024-02-07 Local merge main_c3
2024-02-07 Fixed faulty GPIO# for LED indicator
2024-02-11 UnityChanges
2024-02-11 Removed unity App to fix submodules
2024-02-12 Schematic ready for layout
2024-02-14 implemented UDPServer
2024-02-15 Added ESP MCU IO details
2024-02-16 started layout
2024-02-16 Update sch & add switch 3d model
2024-02-19 Modified LEDIndicator driver for animations
2024-02-19 Updated LEDIndicator for animations
2024-02-21 Animation managment system
2024-02-21 LED Animation managment system
2024-02-22 Component positioning & PCB sizing
2024-02-25 Initial layout finished
2024-02-26 DRC Corrected & TPs Added
2024-02-27 SCH & PCB Finalized for review
2024-02-29 updated submodule, fixed IMU pin initialization
2024-02-29 Added SBU to USB C
2024-02-29 Added Charger PCB
2024-03-01 Updated/Added Footprints
2024-03-02 hardware timer driven animations, client to server commands, auto-formatting
2024-03-02 Hardware timer based animations, client to server commands, auto-formatting
2024-03-03 Changed Charger PCB MCU to STM32
2024-03-04 UDP Client re-write
2024-03-04 UDP pyCube
2024-03-04 UDP Server re-write, RTOS tick rate modified to 1000Hz
2024-03-04 Charger PCB Update
2024-03-05 SCH & PCB Updated
2024-03-06 PCB Layout Finalized
2024-03-06 Vias updated to plugged 0.3mm & Gerbers Finalized
2024-03-06 Updated bno submodule, IMU sampling rate, packet transmit rate, moving Software to new branch
2024-03-06 Updated submodule, IMU sampe rate, packet transmit rate,Software to new branch
2024-03-06 Cleared repo
2024-03-06 Migrated Unity Projects
2024-03-06 Unique device hardware ID
2024-03-06 Unique device hardware IDs
2024-03-07 Updated testing scripts
2024-03-07 Finalized PCBs & Generated Gerbers
2024-03-08 Unity Copy
2024-03-08 Component ordering information finalized
2024-03-08 Unity
2024-03-08 Removed old projects
2024-03-08 New Unity App
2024-03-09 broadcast tests
2024-03-16 Corrected model colors & updated readme
2024-03-21 Broadcast discovery, dynamic retransmit delay
2024-03-21 UDP Broadcast discovery, dynamic retransmit delay to prevent collision
2024-03-21 cleared app for recommit
2024-03-21 Multithreaded UDP client
2024-03-21 main_c3 local merge, prep for hardware
2024-03-21 Pin definitions to reflect hardware, print ID on boot
2024-03-21 fixed WS281B driver
2024-03-21 Deleted submodules for update
2024-03-22 Custom hardware IDs
2024-03-22 Burnt HW IDs
2024-03-22 Removed the store
2024-03-22 New hardware ID system
2024-03-22 UART pin change to account for incorrect dock usb footprint
2024-03-22 Added dock FW
2024-03-22 Added incorrect FP warning
2024-03-22 Added individual port current sense
2024-03-23 Added OLED driver
2024-03-24 Added Chase Animation
2024-03-24 PowerManager, BatteryMonitor, autoformatting changes
2024-03-25 Switch driver, auto formatter, corrected PowerDriver init
2024-04-04 Correct PowerManager init, modified UDP server
2024-04-04 Removed old unity project
2024-04-04 Updated IMUDataGrabber
2024-04-04 Updated documentation
2024-04-04 added battery cutoff voltage shutodwn
2024-05-04 Updated UDPServer, battery SOC & animation, stability fixes
